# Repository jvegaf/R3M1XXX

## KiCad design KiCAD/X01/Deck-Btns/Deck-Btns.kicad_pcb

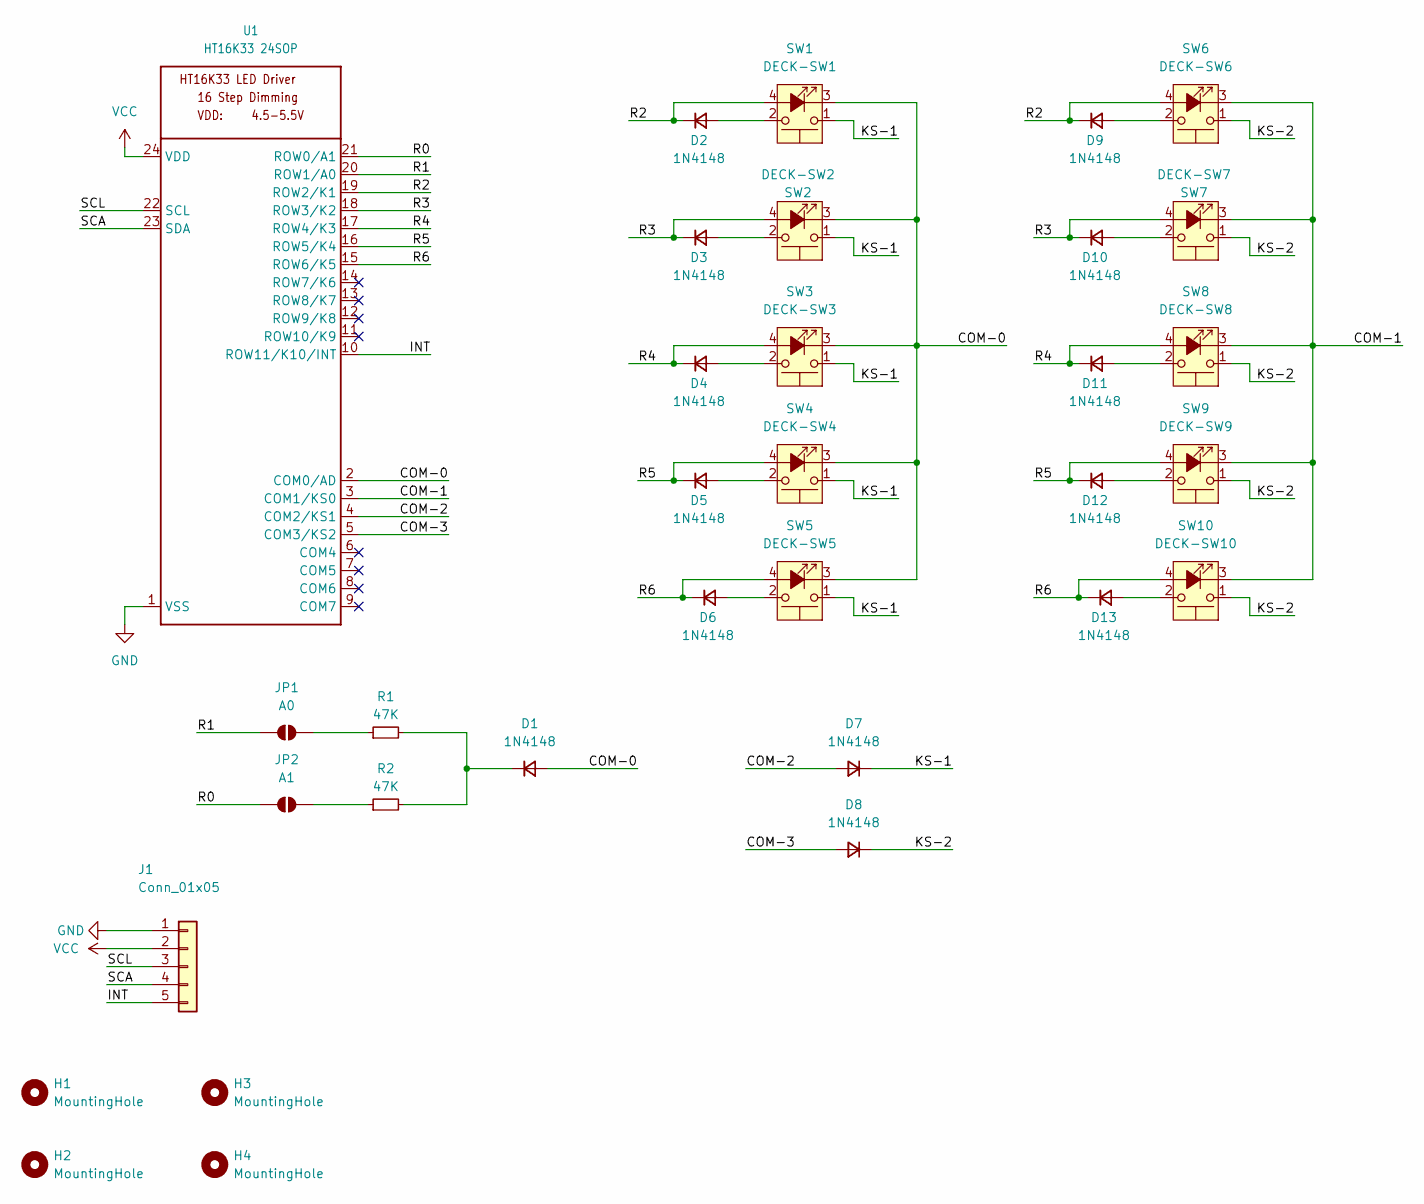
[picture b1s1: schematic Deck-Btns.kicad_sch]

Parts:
D1, D2, D3, D4, D5, D6, D7, D8, D9, D10, D11, D12, D13: 1N4148; D_SOD-123
H1, H2, H3, H4: MountingHole; MountingHole_3.2mm_M3
J1: Conn_01x05; PinHeader_1x05_P2.54mm_Vertical
JP1: A0; SolderJumper-2_P1.3mm_Open_RoundedPad1.0x1.5mm
JP2: A1; SolderJumper-2_P1.3mm_Open_RoundedPad1.0x1.5mm
R1, R2: 47K; R_0805_2012Metric_Pad1.20x1.40mm_HandSolder
SW1: DECK-SW1; led switch
SW2: DECK-SW2; led switch
SW3: DECK-SW3; led switch
SW4: DECK-SW4; led switch
SW5: DECK-SW5; led switch
SW6: DECK-SW6; led switch
SW7: DECK-SW7; led switch
SW8: DECK-SW8; led switch
SW9: DECK-SW9; led switch
SW10: DECK-SW10; led switch
U1: HT16K33 24SOP; SSOP-24_5.3x8.2mm_P0.65mm

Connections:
/COM-0: D1.2 (A), SW1.3 (K), SW2.3 (K), SW3.3 (K), SW4.3 (K), SW5.3 (K), U1.2 (COM0/AD)
/COM-1: SW6.3 (K), SW7.3 (K), SW8.3 (K), SW9.3 (K), SW10.3 (K), U1.3 (COM1/KS0)
/COM-2: D7.2 (A), U1.4 (COM2/KS1)
/COM-3: D8.2 (A), U1.5 (COM3/KS2)
/INT: J1.5, U1.10 (ROW11/K10/INT)
/KS-1: D7.1 (K), SW1.1, SW2.1, SW3.1, SW4.1, SW5.1
/KS-2: D8.1 (K), SW6.1, SW7.1, SW8.1, SW9.1, SW10.1
/R0: JP2.1 (A), U1.21 (ROW0/A1)
/R1: JP1.1 (A), U1.20 (ROW1/A0)
/R2: D2.1 (K), D9.1 (K), SW1.4 (A), SW6.4 (A), U1.19 (ROW2/K1)
/R3: D3.1 (K), D10.1 (K), SW2.4 (A), SW7.4 (A), U1.18 (ROW3/K2)
/R4: D4.1 (K), D11.1 (K), SW3.4 (A), SW8.4 (A), U1.17 (ROW4/K3)
/R5: D5.1 (K), D12.1 (K), SW4.4 (A), SW9.4 (A), U1.16 (ROW5/K4)
/R6: D6.1 (K), D13.1 (K), SW5.4 (A), SW10.4 (A), U1.15 (ROW6/K5)
/SCA: J1.4, U1.23 (SDA)
/SCL: J1.3, U1.22 (SCL)
GND: J1.1, U1.1 (VSS)
unnamed: D1.1 (K), R1.2, R2.2
unnamed: D2.2 (A), SW1.2
unnamed: D3.2 (A), SW2.2
unnamed: D4.2 (A), SW3.2
unnamed: D5.2 (A), SW4.2
unnamed: D6.2 (A), SW5.2
unnamed: D9.2 (A), SW6.2
unnamed: D10.2 (A), SW7.2
unnamed: D11.2 (A), SW8.2
unnamed: D12.2 (A), SW9.2
unnamed: D13.2 (A), SW10.2
unnamed: JP1.2 (B), R1.1
unnamed: JP2.2 (B), R2.1
VCC: J1.2, U1.24 (VDD)

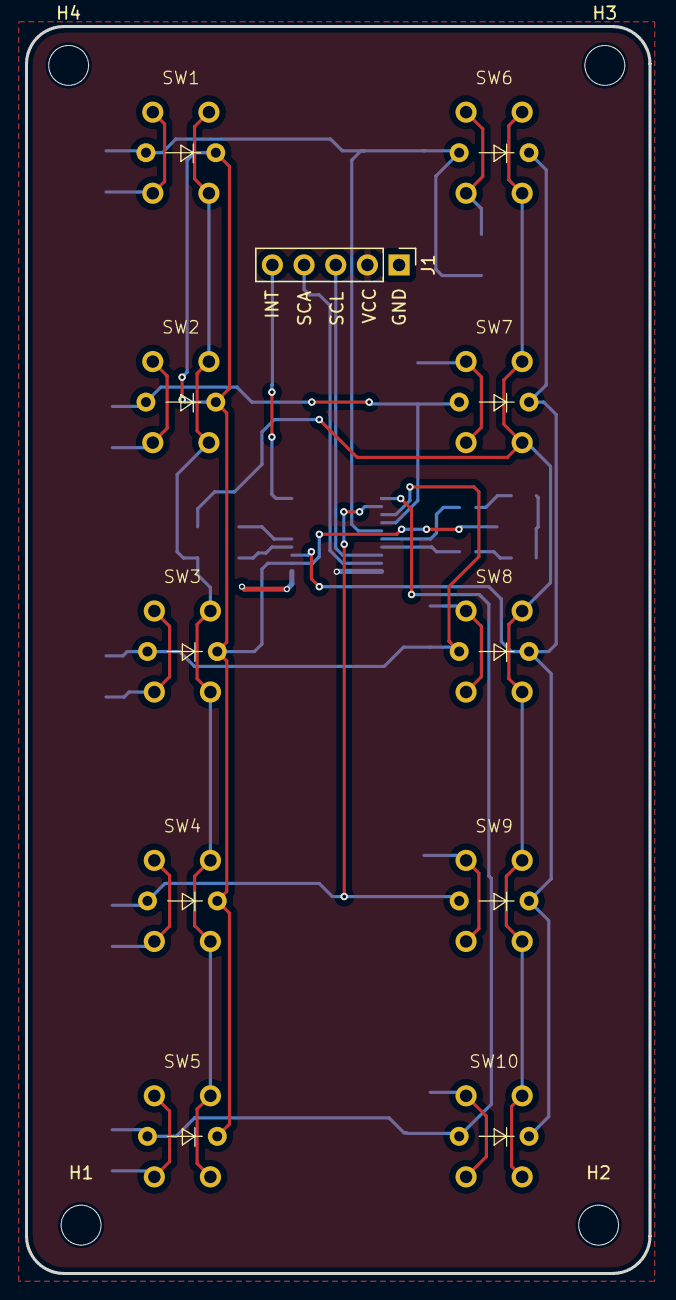
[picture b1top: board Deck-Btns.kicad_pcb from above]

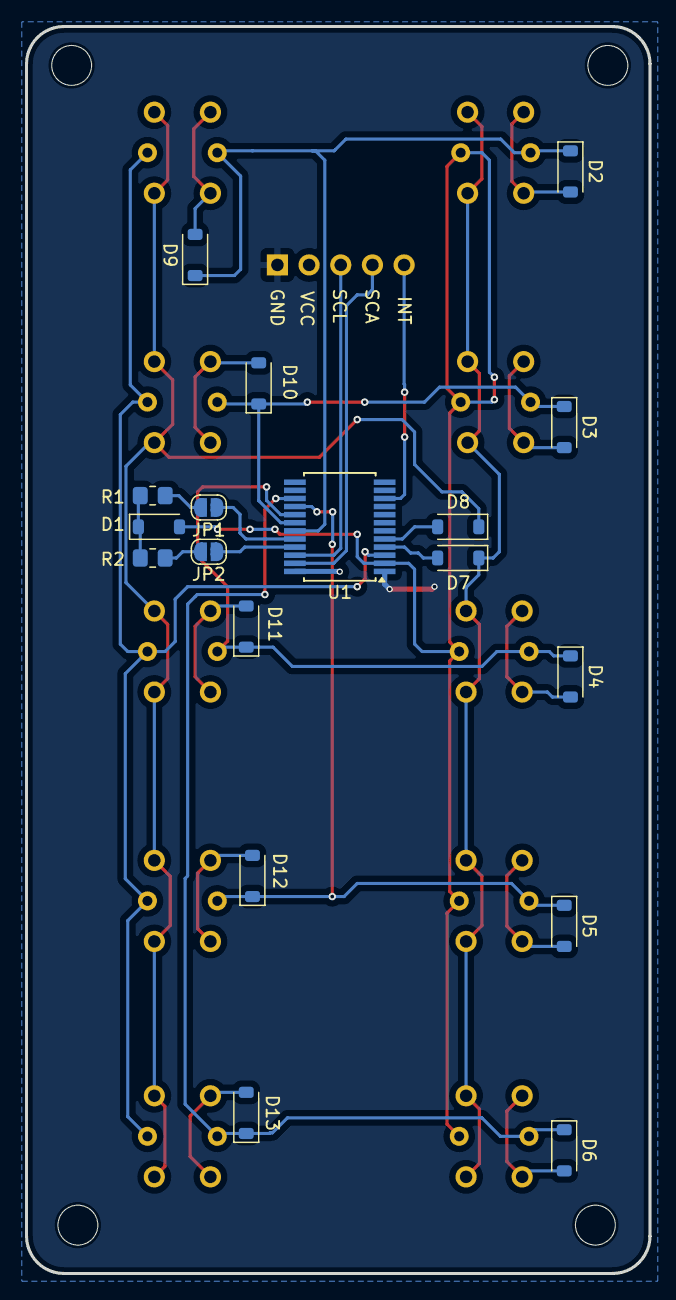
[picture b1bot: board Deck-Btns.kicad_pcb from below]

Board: 2 copper layers, 50.0 x 100.0 mm, 33 parts (18 on the bottom side), 31 nets.

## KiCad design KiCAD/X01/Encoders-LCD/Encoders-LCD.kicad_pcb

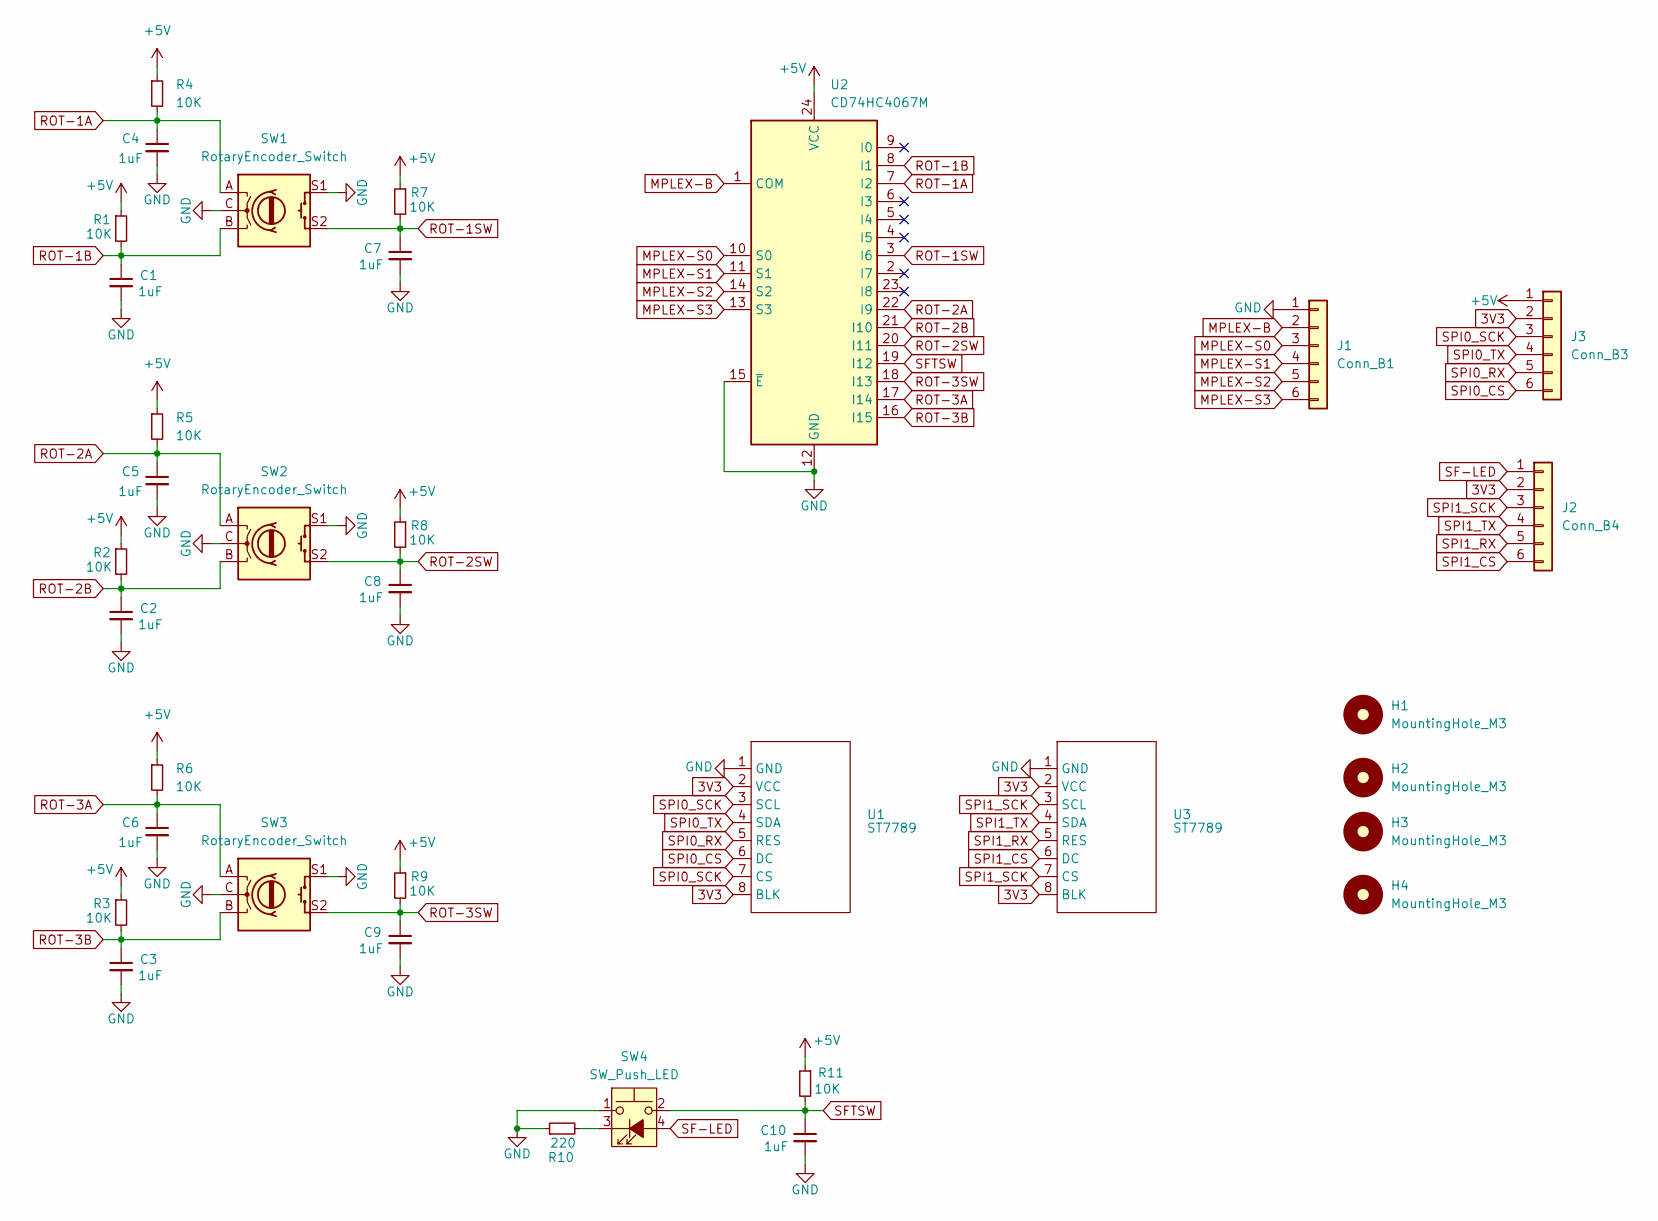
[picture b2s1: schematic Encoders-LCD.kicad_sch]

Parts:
C1, C2, C3, C4, C5, C6, C7, C8, C9, C10: 1uF; C_1206_3216Metric_Pad1.33x1.80mm_HandSolder
H1, H2, H3, H4: MountingHole_M3; MountingHole_3.2mm_M3
J1: Conn_B1; PinHeader_1x06_P2.54mm_Vertical
J2: Conn_B4; PinHeader_1x06_P2.54mm_Vertical
J3: Conn_B3; PinHeader_1x06_P2.54mm_Vertical
R1, R2, R3, R4, R5, R6, R7, R8, R9, R11: 10K; R_1206_3216Metric_Pad1.30x1.75mm_HandSolder
R10: 220; R_1206_3216Metric_Pad1.30x1.75mm_HandSolder
SW1, SW2, SW3: RotaryEncoder_Switch; RotaryEncoder_Alps_EC11E-Switch_Vertical_H20mm_CircularMoun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
SW4: SW_Push_LED; SW_PUSH_6mm_LED
U1, U3: ST7789; 1.14 7789
U2: CD74HC4067M; SOIC-24W_7.5x15.4mm_P1.27mm

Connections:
3V3: J2.2, J3.2, U1.2 (VCC), U1.8 (BLK), U3.2 (VCC), U3.8 (BLK)
+5V: J3.1, R1.1, R2.1, R3.1, R4.1, R5.1, R6.1, R7.1, R8.1, R9.1, R11.1, U2.24 (VCC)
GND: C1.2, C2.2, C3.2, C4.2, C5.2, C6.2, C7.2, C8.2, C9.2, C10.2, J1.1, R10.1, SW1.C, SW1.S1, SW2.C, SW2.S1, SW3.C, SW3.S1, SW4.1, U1.1 (GND), U2.12 (GND), U2.15 (~E), U3.1 (GND)
MPLEX-B: J1.2, U2.1 (COM)
MPLEX-S0: J1.3, U2.10 (S0)
MPLEX-S1: J1.4, U2.11 (S1)
MPLEX-S2: J1.5, U2.14 (S2)
MPLEX-S3: J1.6, U2.13 (S3)
unnamed: R10.2, SW4.3 (K)
ROT-1A: C4.1, R4.2, SW1.A, U2.7 (I2)
ROT-1B: C1.1, R1.2, SW1.B, U2.8 (I1)
ROT-1SW: C7.1, R7.2, SW1.S2, U2.3 (I6)
ROT-2A: C5.1, R5.2, SW2.A, U2.22 (I9)
ROT-2B: C2.1, R2.2, SW2.B, U2.21 (I10)
ROT-2SW: C8.1, R8.2, SW2.S2, U2.20 (I11)
ROT-3A: C6.1, R6.2, SW3.A, U2.17 (I14)
ROT-3B: C3.1, R3.2, SW3.B, U2.16 (I15)
ROT-3SW: C9.1, R9.2, SW3.S2, U2.18 (I13)
SF-LED: J2.1, SW4.4 (A)
SFTSW: C10.1, R11.2, SW4.2, U2.19 (I12)
SPI0_CS: J3.6, U1.6 (DC)
SPI0_RX: J3.5, U1.5 (RES)
SPI0_SCK: J3.3, U1.3 (SCL), U1.7 (CS)
SPI0_TX: J3.4, U1.4 (SDA)
SPI1_CS: J2.6, U3.6 (DC)
SPI1_RX: J2.5, U3.5 (RES)
SPI1_SCK: J2.3, U3.3 (SCL), U3.7 (CS)
SPI1_TX: J2.4, U3.4 (SDA)

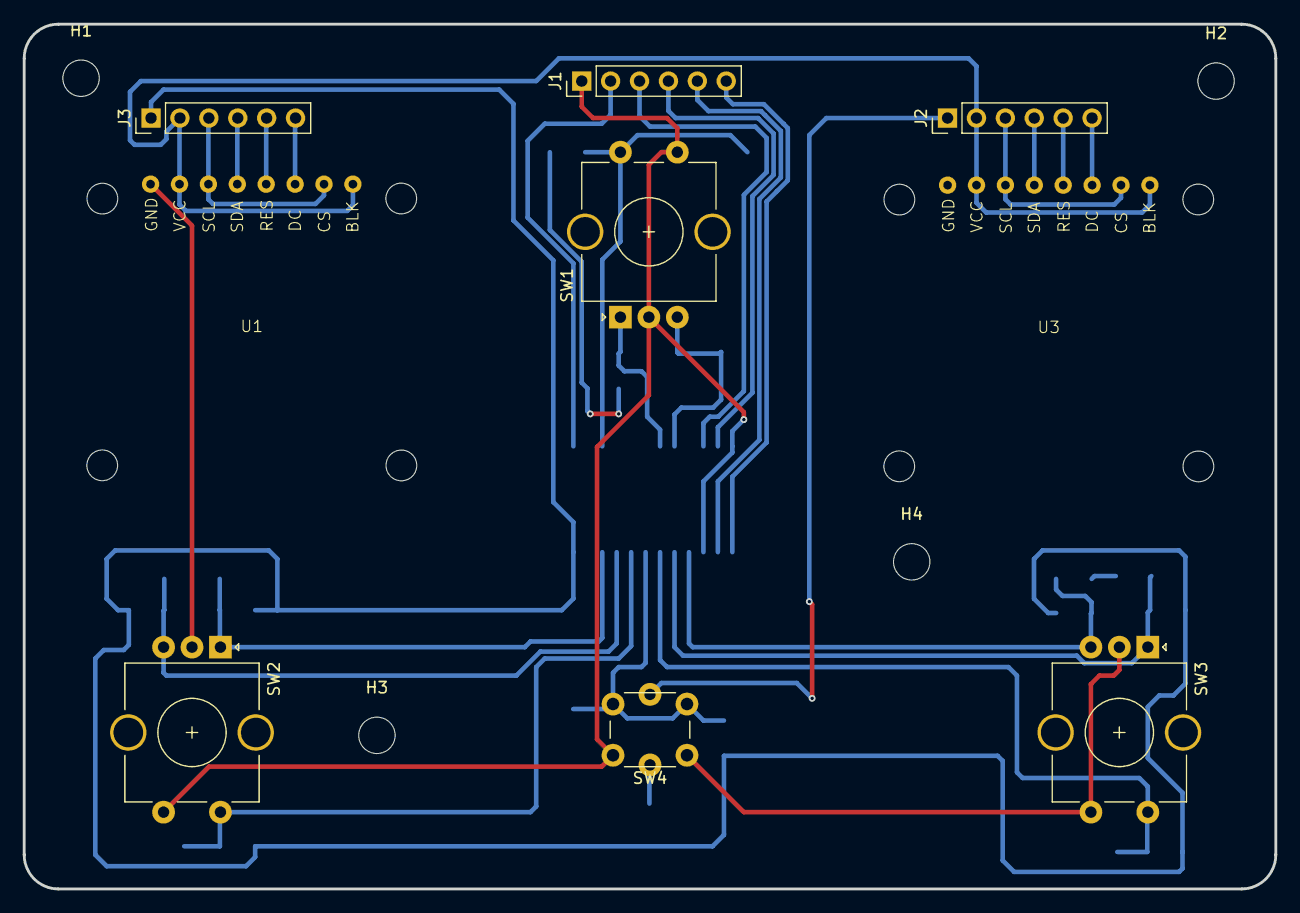
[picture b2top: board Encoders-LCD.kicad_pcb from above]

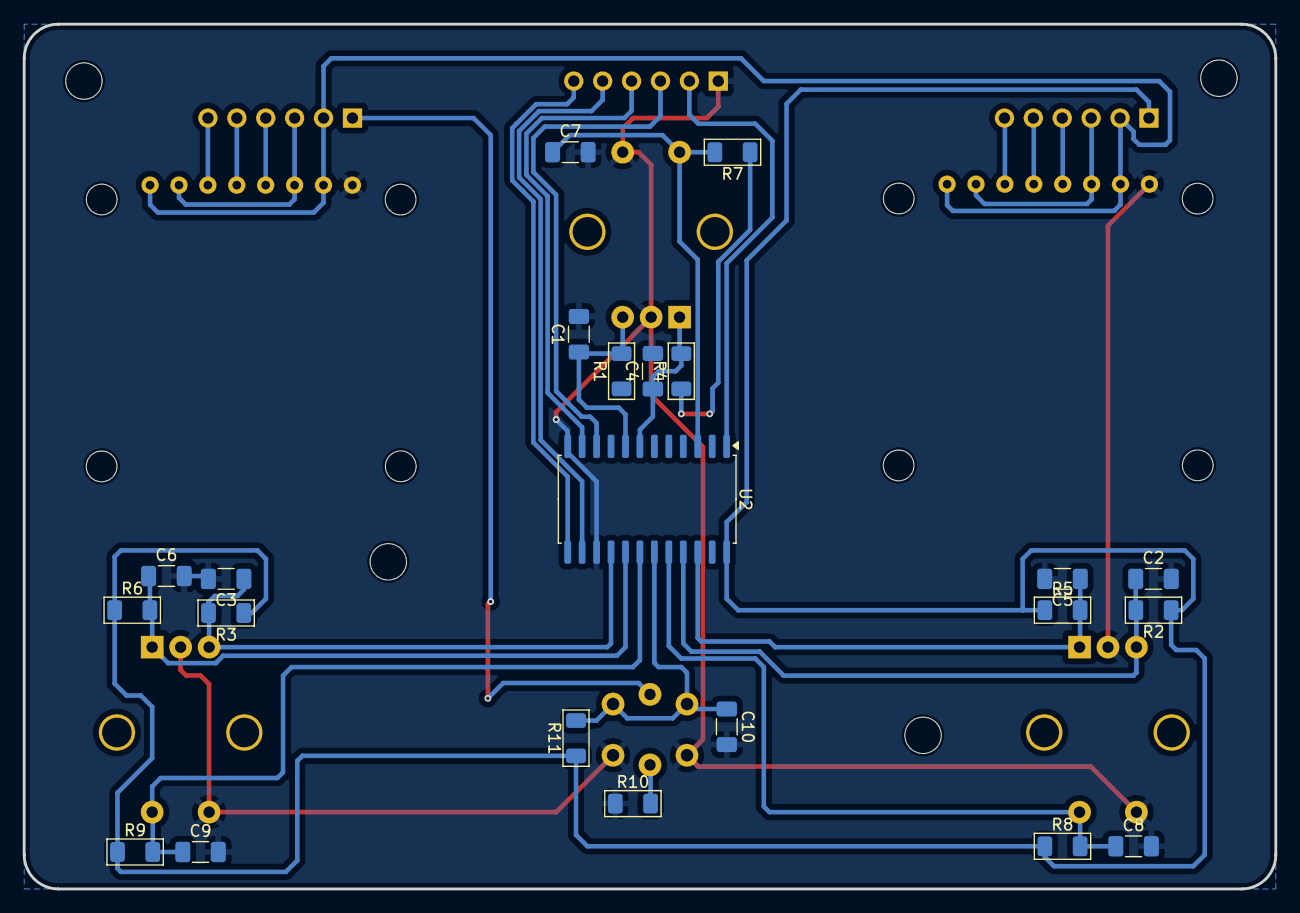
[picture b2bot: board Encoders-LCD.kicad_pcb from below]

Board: 2 copper layers, 110.0 x 76.0 mm, 35 parts (22 on the bottom side), 28 nets.

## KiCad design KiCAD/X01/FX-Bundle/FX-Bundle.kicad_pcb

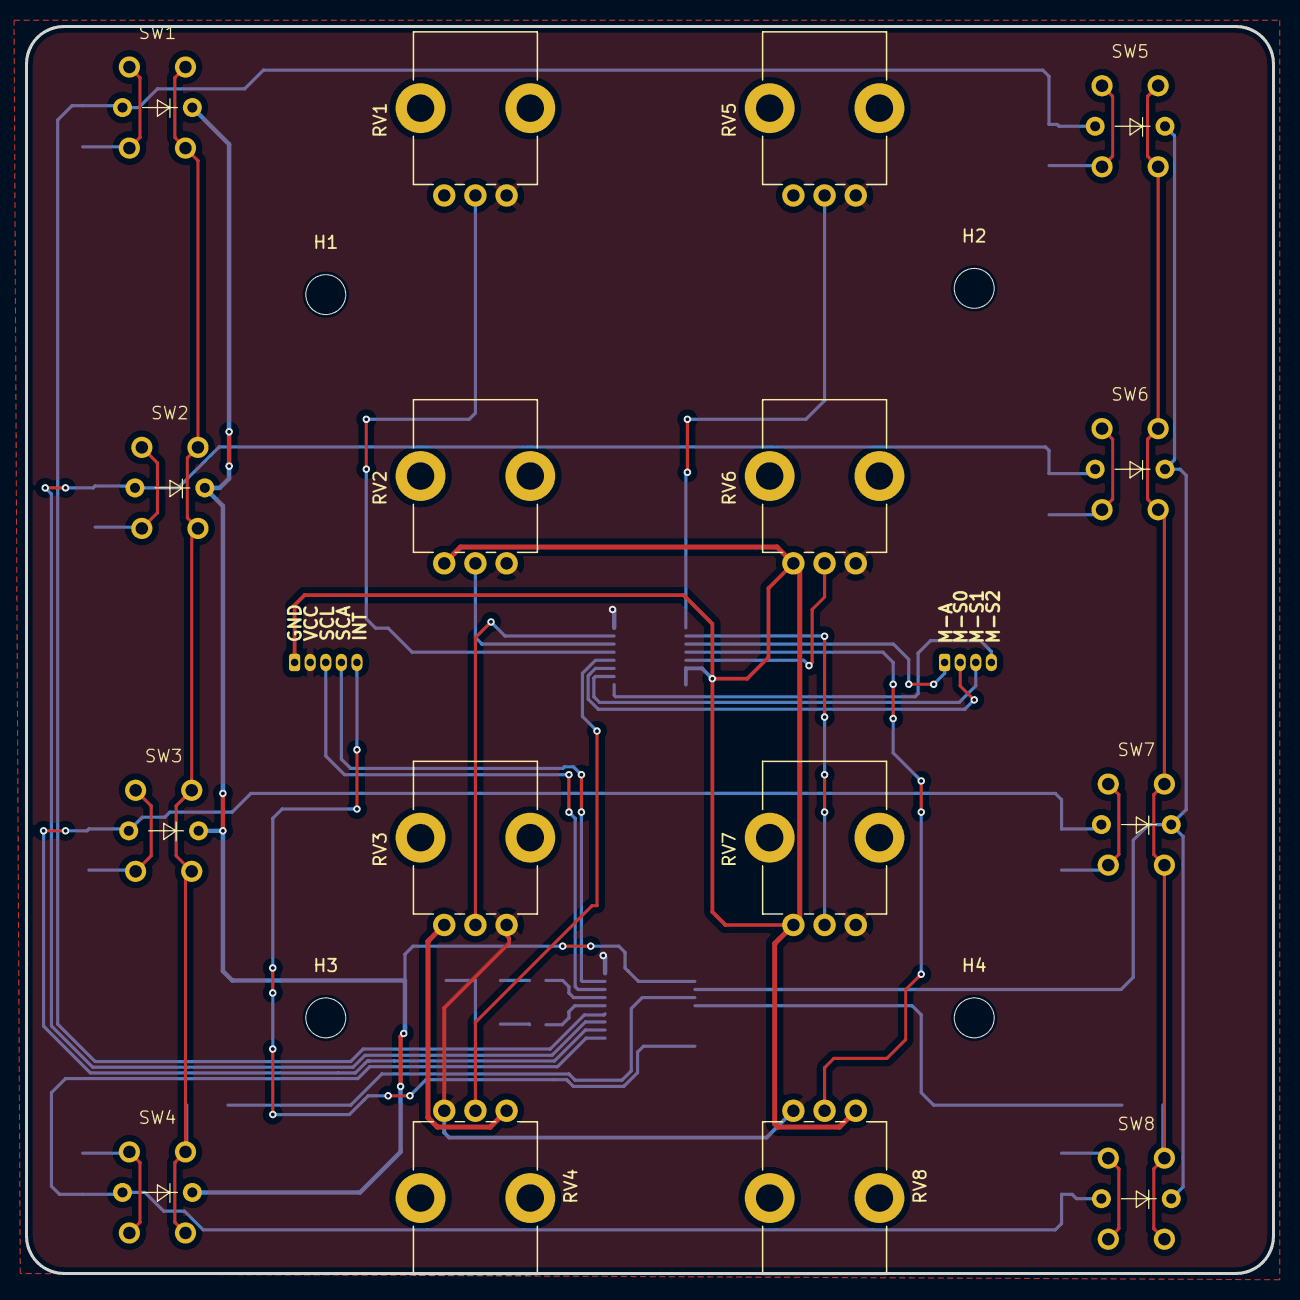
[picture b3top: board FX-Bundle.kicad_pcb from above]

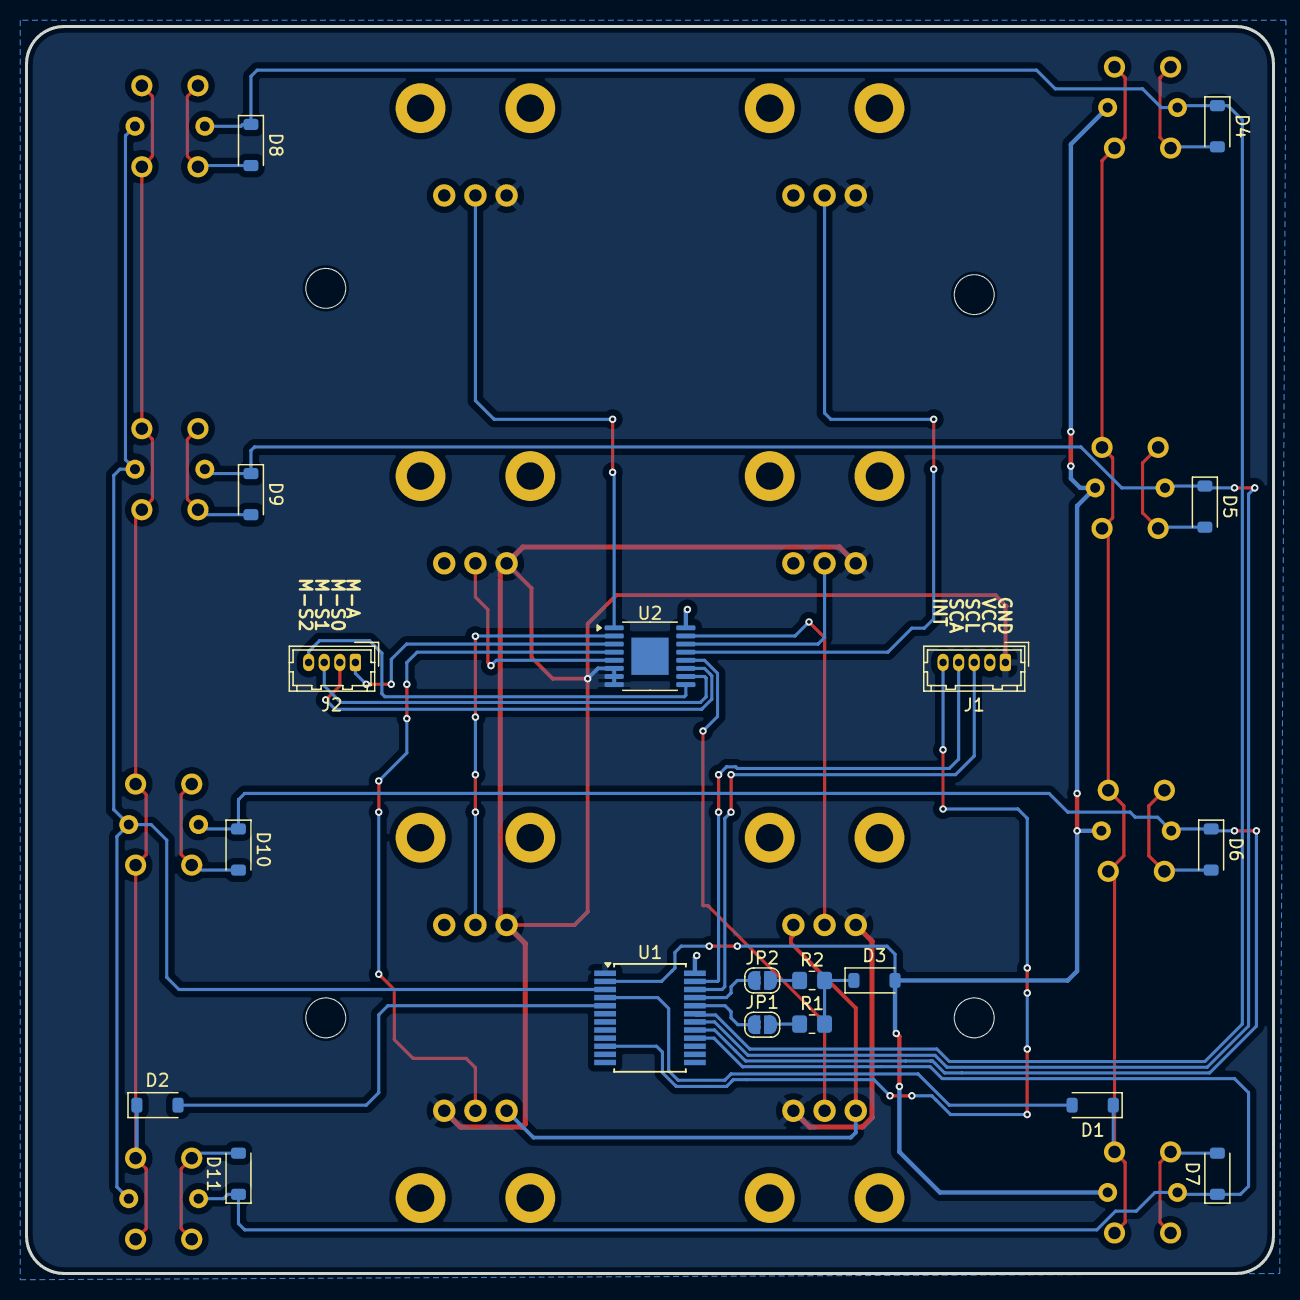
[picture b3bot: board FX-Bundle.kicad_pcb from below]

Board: 2 copper layers, 100.0 x 100.0 mm, 39 parts (19 on the bottom side), 40 nets.

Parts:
D1, D2, D3, D4, D5, D6, D7, D8, D9, D10, D11: 1N4148; D_SOD-123
H1, H2, H3, H4: MountingHole_M3; MountingHole_3.2mm_M3
J1: Conn_I2c; Hirose_DF13-05P-1.25DSA_1x05_P1.25mm_Vertical
J2: Conn_MP; Hirose_DF13-04P-1.25DSA_1x04_P1.25mm_Vertical
JP1: A0; SolderJumper-2_P1.3mm_Open_RoundedPad1.0x1.5mm
JP2: A1; SolderJumper-2_P1.3mm_Open_RoundedPad1.0x1.5mm
R1, R2: 47K; R_0805_2012Metric_Pad1.20x1.40mm_HandSolder
RV1, RV2, RV3, RV4, RV5, RV6, RV7, RV8: R_Pot; Potentiometer_Bourns_PTV09A-1_Single_Vertical
SW1: FX-SW1; led switch
SW2: FX-SW2; led switch
SW3: FX-SW3; led switch
SW4: FX-SW4; led switch
SW5: FX-SW5; led switch
SW6: FX-SW6; led switch
SW7: FX-SW7; led switch
SW8: FX-SW8; led switch
U1: HT16K33 24SOP; SSOP-24_5.3x8.2mm_P0.65mm
U2: 74HC4051; TSSOP-16-1EP_4.4x5mm_P0.65mm_EP3x3mm

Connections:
/COM-0: D3.2 (A), SW1.3 (K), SW2.3 (K), SW3.3 (K), SW4.3 (K), U1.2 (COM0/AD)
/COM-1: SW5.3 (K), SW6.3 (K), SW7.3 (K), SW8.3 (K), U1.3 (COM1/KS0)
/COM-2: D1.2 (A), U1.4 (COM2/KS1)
/COM-3: D2.2 (A), U1.5 (COM3/KS2)
/INT: J1.5, U1.10 (ROW11/K10/INT)
/KS-1: D1.1 (K), SW1.1, SW2.1, SW3.1, SW4.1
/KS-2: D2.1 (K), SW5.1, SW6.1, SW7.1, SW8.1
/MP-A: J2.1, U2.3 (A)
/MP-S0: J2.2, U2.11 (S0)
/MP-S1: J2.3, U2.10 (S1)
/MP-S2: J2.4, U2.9 (S2)
/POT1: RV1.2, U2.13 (A0)
/POT2: RV2.2, U2.14 (A1)
/POT3: RV3.2, U2.15 (A2)
/POT4: RV4.2, U2.12 (A3)
/POT5: RV5.2, U2.1 (A4)
/POT6: RV6.2, U2.5 (A5)
/POT7: RV7.2, U2.2 (A6)
/POT8: RV8.2, U2.4 (A7)
/R0: JP2.1 (A), U1.21 (ROW0/A1)
/R1: JP1.1 (A), U1.20 (ROW1/A0)
/R2: D4.1 (K), D8.1 (K), SW1.4 (A), SW5.4 (A), U1.19 (ROW2/K1)
/R3: D5.1 (K), D9.1 (K), SW2.4 (A), SW6.4 (A), U1.18 (ROW3/K2)
/R4: D6.1 (K), D10.1 (K), SW3.4 (A), SW7.4 (A), U1.17 (ROW4/K3)
/R5: D7.1 (K), D11.1 (K), SW4.4 (A), SW8.4 (A), U1.16 (ROW5/K4)
/SCA: J1.4, U1.23 (SDA)
/SCL: J1.3, U1.22 (SCL)
GND: J1.1, RV1.3, RV2.3, RV3.3, RV4.3, RV5.3, RV6.3, RV7.3, RV8.3, U1.1 (VSS), U2.6 (~E), U2.7 (VEE), U2.8 (GND)
unnamed: D3.1 (K), R1.2, R2.2
unnamed: D4.2 (A), SW1.2
unnamed: D5.2 (A), SW2.2
unnamed: D6.2 (A), SW3.2
unnamed: D7.2 (A), SW4.2
unnamed: D8.2 (A), SW5.2
unnamed: D9.2 (A), SW6.2
unnamed: D10.2 (A), SW7.2
unnamed: D11.2 (A), SW8.2
unnamed: JP1.2 (B), R1.1
unnamed: JP2.2 (B), R2.1
VCC: J1.2, RV1.1, RV2.1, RV3.1, RV4.1, RV5.1, RV6.1, RV7.1, RV8.1, U1.24 (VDD), U2.16 (VCC)

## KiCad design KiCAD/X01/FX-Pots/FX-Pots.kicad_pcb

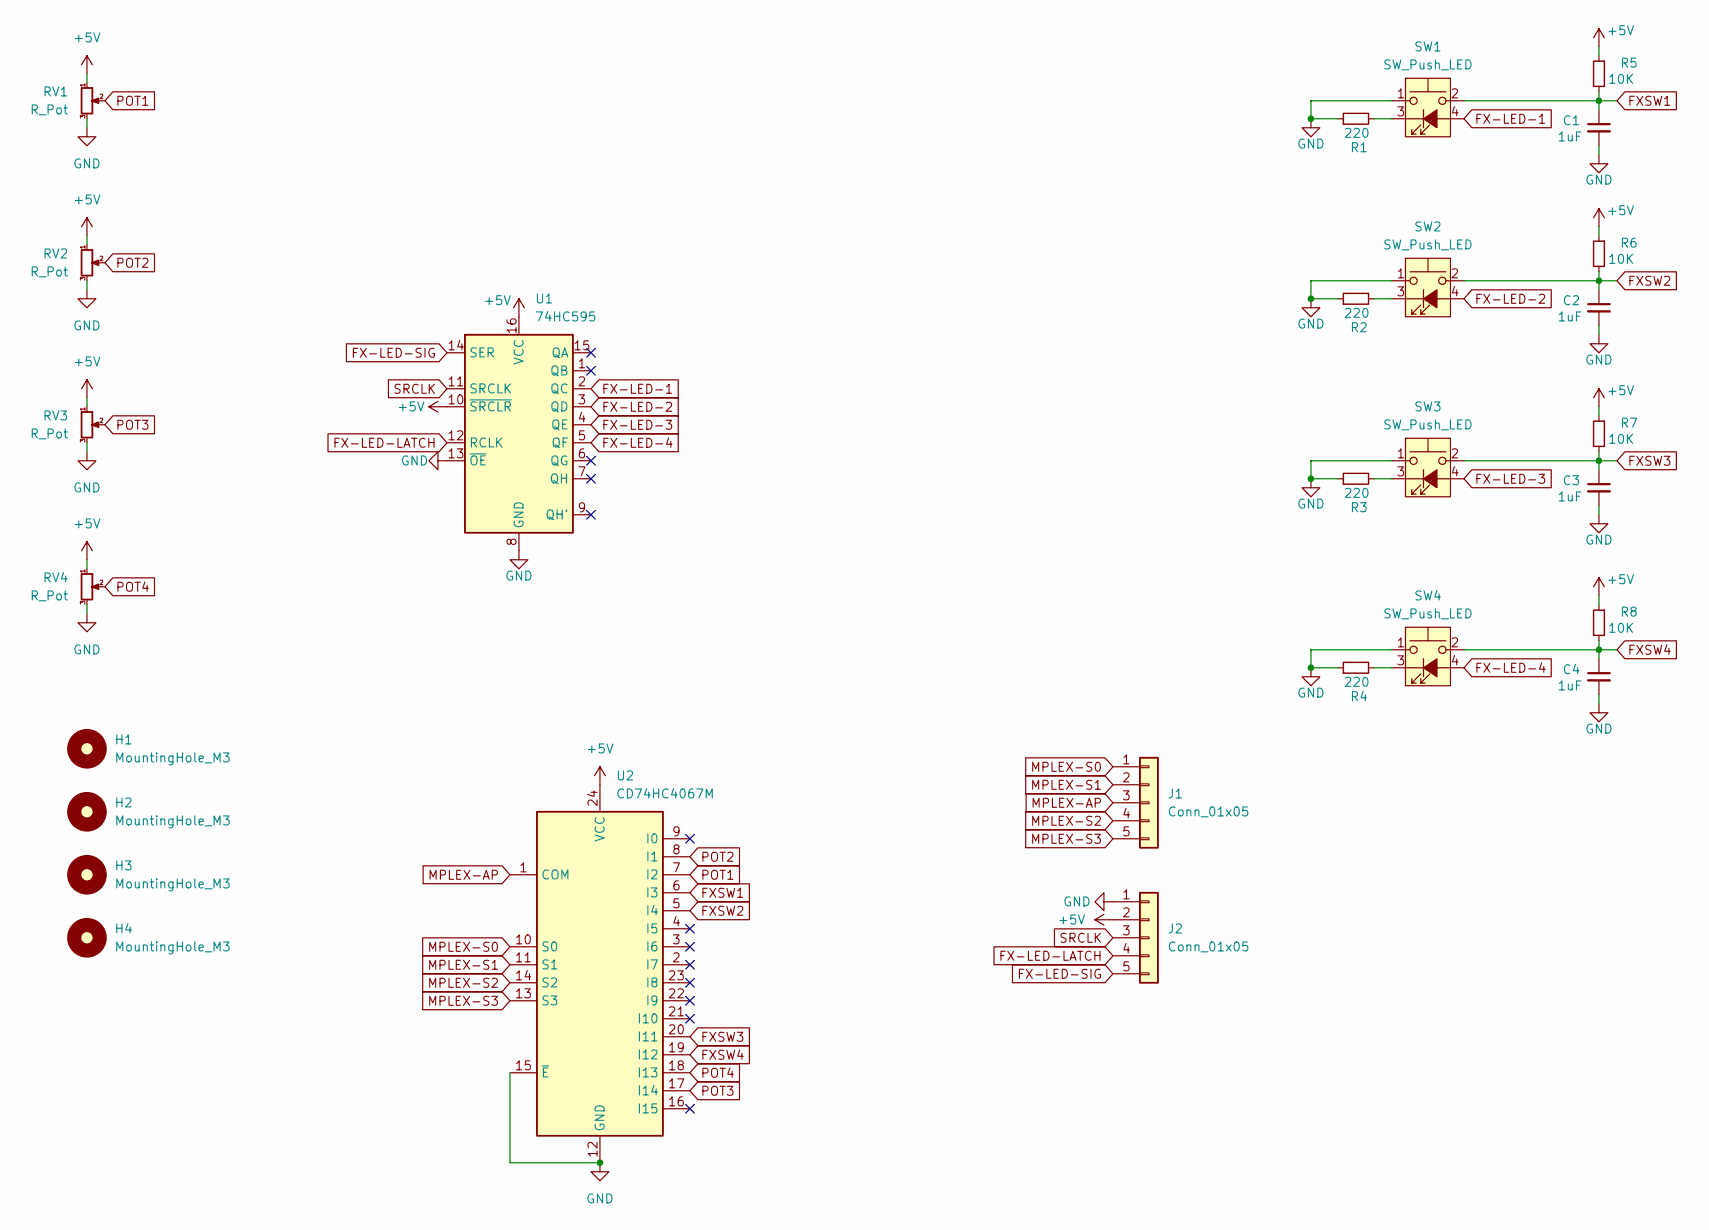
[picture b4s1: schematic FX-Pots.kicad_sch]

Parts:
C1, C2, C3, C4: 1uF; C_1206_3216Metric_Pad1.33x1.80mm_HandSolder
H1, H2, H3, H4: MountingHole_M3; MountingHole_3.2mm_M3
J1, J2: Conn_01x05; PinSocket_1x05_P2.54mm_Vertical
R1, R2, R3, R4: 220; R_1206_3216Metric_Pad1.30x1.75mm_HandSolder
R5, R6, R7, R8: 10K; R_1206_3216Metric_Pad1.30x1.75mm_HandSolder
RV1, RV2, RV3, RV4: R_Pot; Potentiometer_Bourns_PTV09A-1_Single_Vertical
SW1, SW2, SW3, SW4: SW_Push_LED; led switch
U1: 74HC595; SOIC-16_3.9x9.9mm_P1.27mm
U2: CD74HC4067M; SOIC-24W_7.5x15.4mm_P1.27mm

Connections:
+5V: J2.2, R5.1, R6.1, R7.1, R8.1, RV1.1, RV2.1, RV3.1, RV4.1, U1.10 (~SRCLR), U1.16 (VCC), U2.24 (VCC)
FX-LED-1: SW1.4 (A), U1.2 (QC)
FX-LED-2: SW2.4 (A), U1.3 (QD)
FX-LED-3: SW3.4 (A), U1.4 (QE)
FX-LED-4: SW4.4 (A), U1.5 (QF)
FX-LED-LATCH: J2.4, U1.12 (RCLK)
FX-LED-SIG: J2.5, U1.14 (SER)
FXSW1: C1.1, R5.2, SW1.2, U2.6 (I3)
FXSW2: C2.1, R6.2, SW2.2, U2.5 (I4)
FXSW3: C3.1, R7.2, SW3.2, U2.20 (I11)
FXSW4: C4.1, R8.2, SW4.2, U2.19 (I12)
GND: C1.2, C2.2, C3.2, C4.2, J2.1, R1.1, R2.1, R3.1, R4.1, RV1.3, RV2.3, RV3.3, RV4.3, SW1.1, SW2.1, SW3.1, SW4.1, U1.8 (GND), U1.13 (~OE), U2.12 (GND), U2.15 (~E)
MPLEX-AP: J1.3, U2.1 (COM)
MPLEX-S0: J1.1, U2.10 (S0)
MPLEX-S1: J1.2, U2.11 (S1)
MPLEX-S2: J1.4, U2.14 (S2)
MPLEX-S3: J1.5, U2.13 (S3)
unnamed: R1.2, SW1.3 (K)
unnamed: R2.2, SW2.3 (K)
unnamed: R3.2, SW3.3 (K)
unnamed: R4.2, SW4.3 (K)
POT1: RV1.2, U2.7 (I2)
POT2: RV2.2, U2.8 (I1)
POT3: RV3.2, U2.17 (I14)
POT4: RV4.2, U2.18 (I13)
SRCLK: J2.3, U1.11 (SRCLK)

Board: 2 copper layers, 28 parts (14 on the bottom side), 26 nets, no tracks yet.
